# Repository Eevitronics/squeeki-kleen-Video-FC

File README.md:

# squeeki-kleen-Video-FC

> **Note:** This is a modified version of [squeeki-kleen Video FC](https://github.com/Gumball2415/squeeki-kleen-Video-FC) by Persune, adapted by Eevitronics. The MMCX connector has been replaced with solder-wire pads. See [CHANGES.md](CHANGES.md) for the full list of modifications, which are licensed under the TAPR Open Hardware License.

An open source hardware external composite video bypass preamplifier modboard
for the Famicom/NES

## Buy assembled boards

Assembled boards of this Eevitronics version are available from the
[Eevitronics Store](https://www.eevitronics.jp). Full design files, including
Gerbers and BOM, remain freely available in this repository under the TAPR
Open Hardware License.

This version is not affiliated with or supported by Persune. For support with
Eevitronics boards, please contact Eevitronics.

## About

I made a compact daughterboard composite video output based on the
[composite amplifier circuit from the AV Famicom](https://www.nesdev.org/wiki/PPU_pinout#Composite_Video_Output).
This is designed to make AV modding RF-only consoles such as the RF Famicom and the Toploading NES-101 compact and simple.

## How to install

TODO: image demonstrations.

1. If your board does not have tented vias, cover the area underneath the PPU with insulating tape. Be sure to also cover underneath the video/ground wire pads to avoid shorts.
2. To reduce stray inductive connections, isolate pin 21 of the PPU by cutting any traces connecting to it as close to the through-hole pad as much as possible.
3. If needed, add additional bypass capacitors in the empty C3 and C4 footprints.

## PCB specifications

Note that this project is optimized for JLCPCB manufacturing.

- 2 layers
- 50.80 x 17.78 mm
- 0.8 mm thickness
- Any surface finish
- Any soldermask/silkscreen color
- Tented vias
	- alternatively, cover area under board with kapton/insulative tape

## License

This is licensed under the [TAPR Open Hardware Licence](https://tapr.org/the-tapr-open-hardware-license/). Copyright Persune 2025. Modifications by Eevitronics 2026, see [CHANGES.md](CHANGES.md).

## Credits

Special thanks to:
- The NESDev community for advice and help
- lidnariq for advice
- Finny (grievre/arreffem) for inspiration
- j4m13c0 for testing the board (and notifying me of Q1 pinout error!)

## Support

If you enjoy this project or find it helpful, please support me using the links below!

- 
- [Patreon](https://patreon.com/persune)

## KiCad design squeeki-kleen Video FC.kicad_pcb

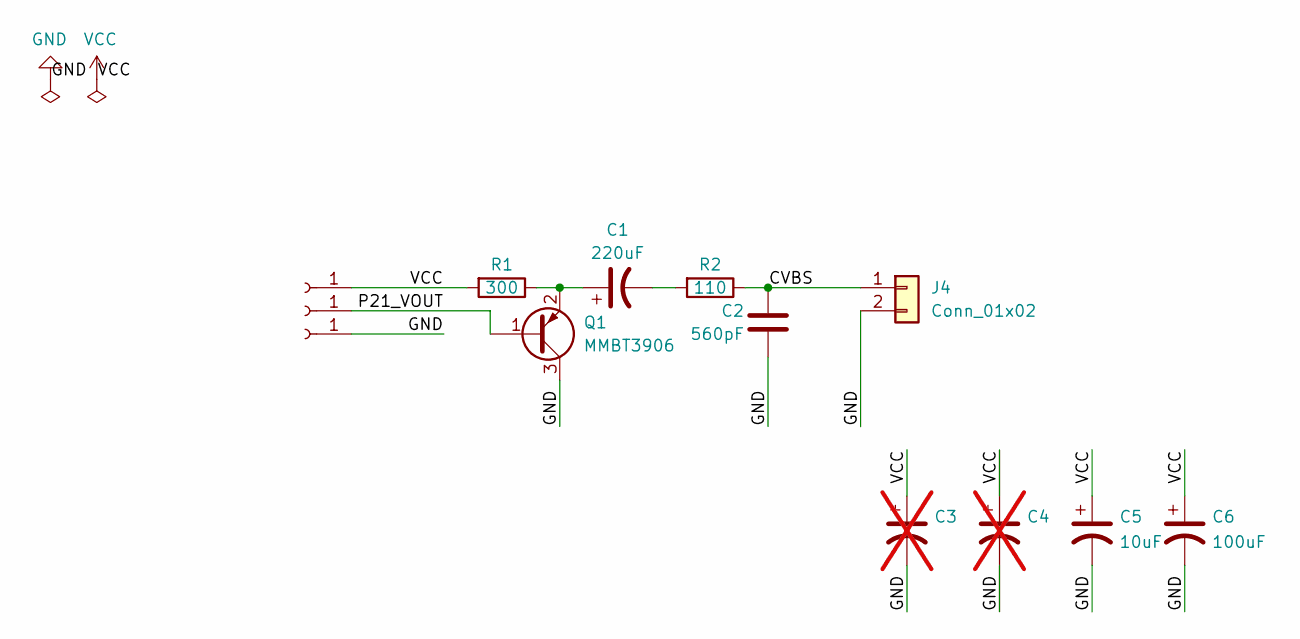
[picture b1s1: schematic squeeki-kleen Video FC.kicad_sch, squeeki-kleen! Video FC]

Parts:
C1: 220uF; CP_Elec_6.3x5.4; LCSC C72494
C2: 560pF; C_0805_2012Metric; LCSC C527188
C3, C4: CP_EIA-3216-18_Kemet-A; LCSC C1508940; not fitted
C5: 10uF; CP_EIA-3216-18_Kemet-A; LCSC C1508940
C6: 100uF; CP_Elec_6.3x4.5; LCSC C5374788
J1: VCC; THT_Hole
J2: VOUT; THT_Hole
J3: GND; THT_Hole
J4: Conn_01x02; SolderWire-0.25sqmm_1x02_P4.2mm_D0.65mm_OD1.7mm
Q1: MMBT3906; SOT-23; LCSC C2891809
R1: 300; R_0805_2012Metric; LCSC C17617
R2: 110; R_0805_2012Metric; LCSC C229072

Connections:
/CVBS: C2.1, J4.1, R2.1; also elsewhere on the board
/P21_VOUT: J2.1 (Pin_1_1), Q1.1 (B)
GND: C2.2, C3.2, C4.2, C5.2, C6.2, J3.1 (Pin_1_1), J4.2, Q1.3 (C); also elsewhere on the board
unnamed: C1.2, R2.2
unnamed: C1.1, Q1.2 (E), R1.1
VCC: C3.1, C4.1, C5.1, C6.1, J1.1 (Pin_1_1), R1.2

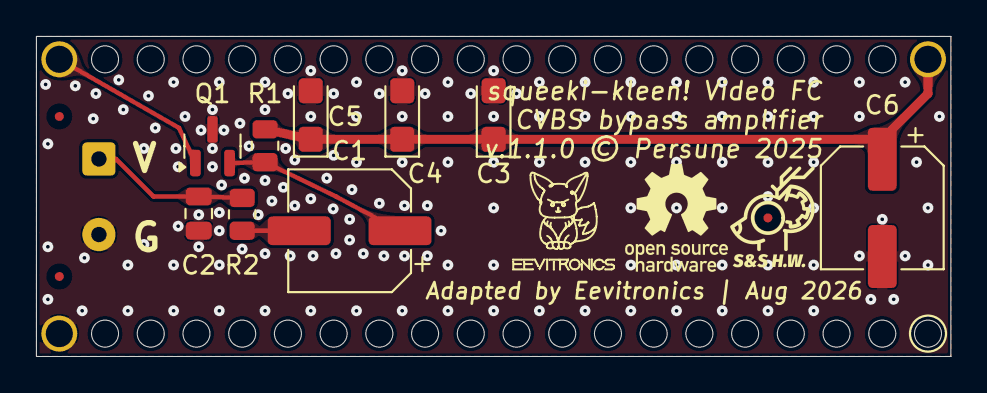
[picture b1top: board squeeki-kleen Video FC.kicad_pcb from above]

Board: 2 copper layers, 50.8 x 17.8 mm, 15 parts (0 on the bottom side), 6 nets.

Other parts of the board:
GND: Conn_01x02; SolderWire-0.25sqmm_1x02_P4.2mm_D0.65mm_OD1.7mm
svg2mod: G***; maustech icon fiducial 0-50mm 1-50mm
svg2mod#2: G***; oshw-logo 6x6mm

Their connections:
/CVBS: GND.1; also elsewhere on the board
GND: GND.2; also elsewhere on the board

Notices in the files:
squeeki-kleen Video FC.kicad_pcb:
v.1.1.0 © Persune 2025
